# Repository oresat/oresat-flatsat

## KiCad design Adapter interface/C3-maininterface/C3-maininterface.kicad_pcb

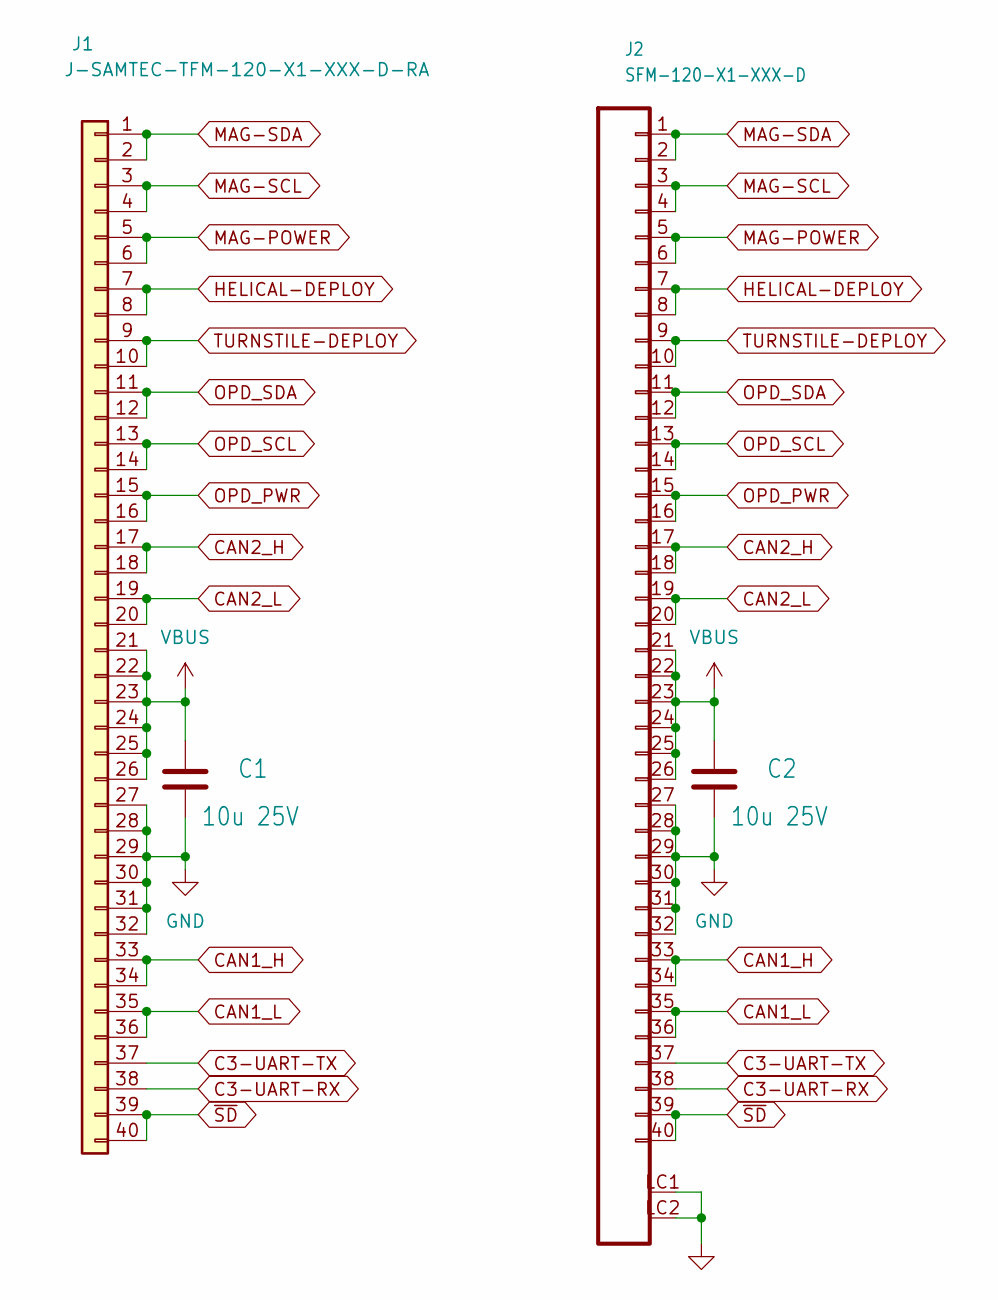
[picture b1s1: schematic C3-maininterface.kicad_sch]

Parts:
C1, C2: 10u 25V; C_1206_3216Metric
J1: J-SAMTEC-TFM-120-X1-XXX-D-RA; MPN TFM-120-01-L-D-RA
J2: SFM-120-X1-XXX-D; J-SAMTEC-SFM-120-X1-XXX-D

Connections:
C3-UART-RX: J1.38, J2.38
C3-UART-TX: J1.37, J2.37
CAN1_H: J1.33, J1.34, J2.33, J2.34
CAN1_L: J1.35, J1.36, J2.35, J2.36
CAN2_H: J1.17, J1.18, J2.17, J2.18
CAN2_L: J1.19, J1.20, J2.19, J2.20
GND: C1.2, C2.2, J1.27, J1.28, J1.29, J1.30, J1.31, J1.32, J2.27, J2.28, J2.29, J2.30, J2.31, J2.32, J2.LC1, J2.LC2
HELICAL-DEPLOY: J1.7, J1.8, J2.7, J2.8
MAG-POWER: J1.5, J1.6, J2.5, J2.6
MAG-SCL: J1.3, J1.4, J2.3, J2.4
MAG-SDA: J1.1, J1.2, J2.1, J2.2
OPD_PWR: J1.15, J1.16, J2.15, J2.16
OPD_SCL: J1.13, J1.14, J2.13, J2.14
OPD_SDA: J1.11, J1.12, J2.11, J2.12
TURNSTILE-DEPLOY: J1.9, J1.10, J2.9, J2.10
VBUS: C1.1, C2.1, J1.21, J1.22, J1.23, J1.24, J1.25, J1.26, J2.21, J2.22, J2.23, J2.24, J2.25, J2.26
~SD: J1.39, J1.40, J2.39, J2.40

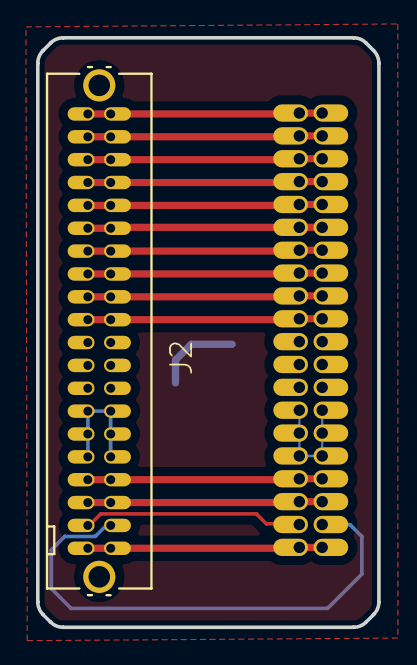
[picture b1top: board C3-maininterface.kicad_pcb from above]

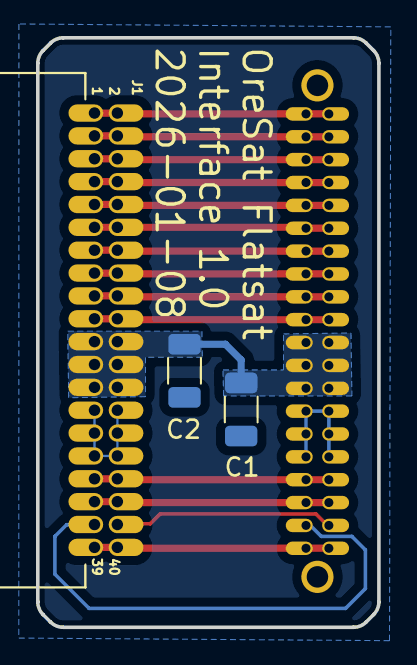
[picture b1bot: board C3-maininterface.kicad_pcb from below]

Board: 4 copper layers, 19.0 x 32.8 mm, 4 parts (3 on the bottom side), 17 nets.

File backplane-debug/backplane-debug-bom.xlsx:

OreSat Backplane Debug Connector Board v2.0
Qty | Parts | MFR | MPN | Description | DIST | DPN | DIST2 | DPN2 | DNS
1 | J1 | Harwin Inc. | M55-7101642R | CONN HEADER SMD R/A 16POS 1.27MM | Digi-Key | 952-3892-1-ND |  |  | DNS
1 | J2 | Amphenol ICC (FCI) | 86130161014345E1LF | QKE CONN SOCKET IDC 16 POS 2.54MM | Digi-Key | 609-86130161014345E1LF-ND

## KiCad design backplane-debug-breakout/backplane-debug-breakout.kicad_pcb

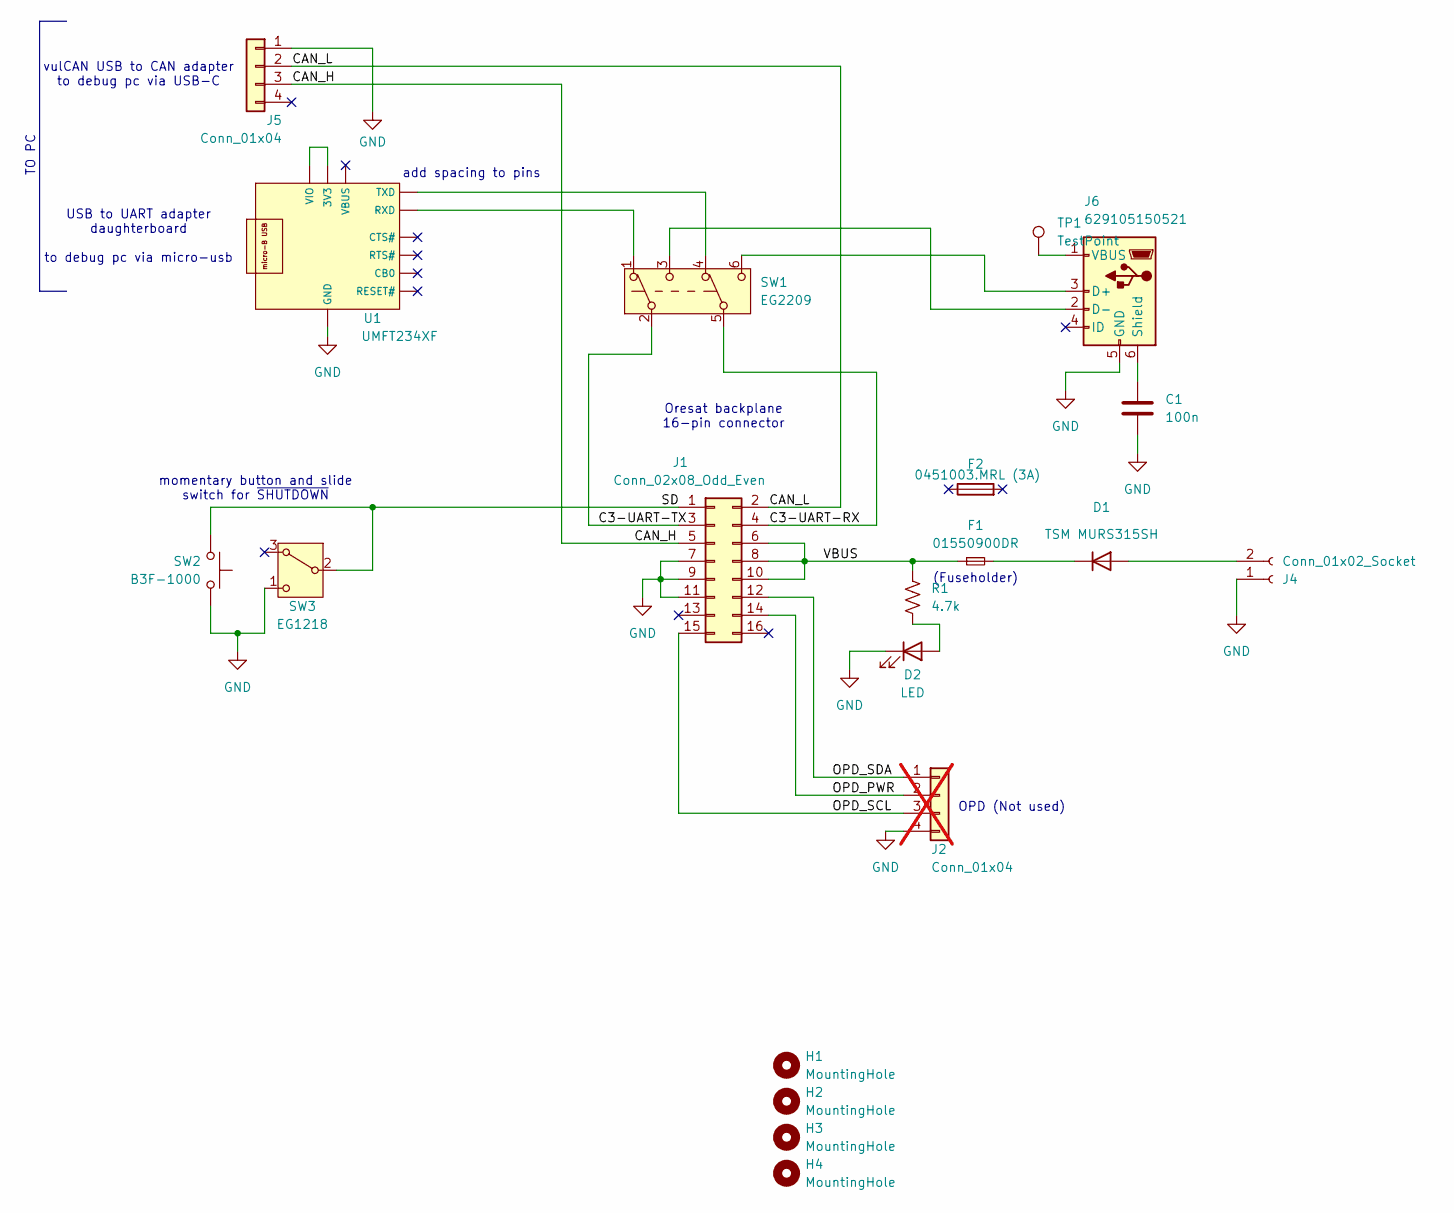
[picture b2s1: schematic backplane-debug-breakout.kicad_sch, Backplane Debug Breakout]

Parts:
C1: 100n; C_0603_1608Metric; MPN TMK107BJ104KAHT
D1: TSM MURS315SH; Diode TSM MURS315SH; MPN MUR315SH
D2: LED; LED_0603_1608Metric_Pad1.05x0.95mm_HandSolder; MPN 150060RS75000
F1: 01550900DR; Littelfuse 155900DR; MPN 01550900DR
F2: 0451003.MRL (3A); MPN 0451003.MRL
H1, H2, H3, H4: MountingHole; MountingHole_3mm_no_copper
J1: Conn_02x08_Odd_Even; IDC-Header_2x08_P2.54mm_Vertical; MPN 61201621621
J2: Conn_01x04; PinHeader_1x04_P2.54mm_Vertical; MPN 0757570441; not fitted
J4: Conn_01x02_Socket; PHOENIX_1995499; MPN 1995499
J5: Conn_01x04; PinHeader_1x04_P2.54mm_Vertical; MPN 0757570441
J6: 629105150521; USB_Micro-B_Wuerth_629105150521_CircularHoles; MPN 629105150521
R1: 4.7k; R_0603_1608Metric_Pad0.98x0.95mm_HandSolder; MPN RMCF0603FT4K70
SW1: EG2209; EG2209 DPDT; MPN EG2209
SW2: B3F-1000; SW_PUSH_6mm; MPN B3F-1000
SW3: EG1218; PinHeader_1x03_P2.54mm_Vertical; MPN EG1218
TP1: TestPoint; TestPoint-0.75mm-th
U1: UMFT234XF; MPN UMFT234XF

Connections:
/C3-UART-RX: J1.4, SW1.5 (B)
/C3-UART-TX: J1.3, SW1.2 (B)
/CAN_H: J1.5, J5.3
/CAN_L: J1.2, J5.2
/OPD_PWR: J1.14, J2.2
/OPD_SCL: J1.15, J2.3
/OPD_SDA: J1.12, J2.1
/SD: J1.1, SW2.2, SW3.2 (B)
/VBUS: F1.1, J1.6, J1.8, J1.10, R1.1
GND: C1.2, D2.1 (K), J1.7, J1.9, J1.11, J2.4, J4.1, J5.1, J6.5 (GND), SW2.1, SW3.1 (C), U1.P4 (GND)
unnamed: D1.2 (A), J4.2
unnamed: D1.1 (K), F1.2
unnamed: D2.2 (A), R1.2
unnamed: J6.3 (D+), SW1.6 (C)
unnamed: J6.2 (D-), SW1.3 (C)
unnamed: C1.1, J6.6 (Shield)
unnamed: J6.1 (VBUS), TP1.1
unnamed: U1.P2 (3V3), U1.P3 (VIO)
unnamed: SW1.1 (A), U1.P9 (RXD)
unnamed: SW1.4 (A), U1.P7 (TXD)

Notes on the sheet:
Oresat backplane 16-pin connector
vulCAN USB to CAN adapter to debug pc via USB-C
momentary button and slide switch for ~{SHUTDOWN}
TO PC
(Fuseholder)
USB to UART adapter daughterboard to debug pc via micro-usb
add spacing to pins
OPD (Not used)

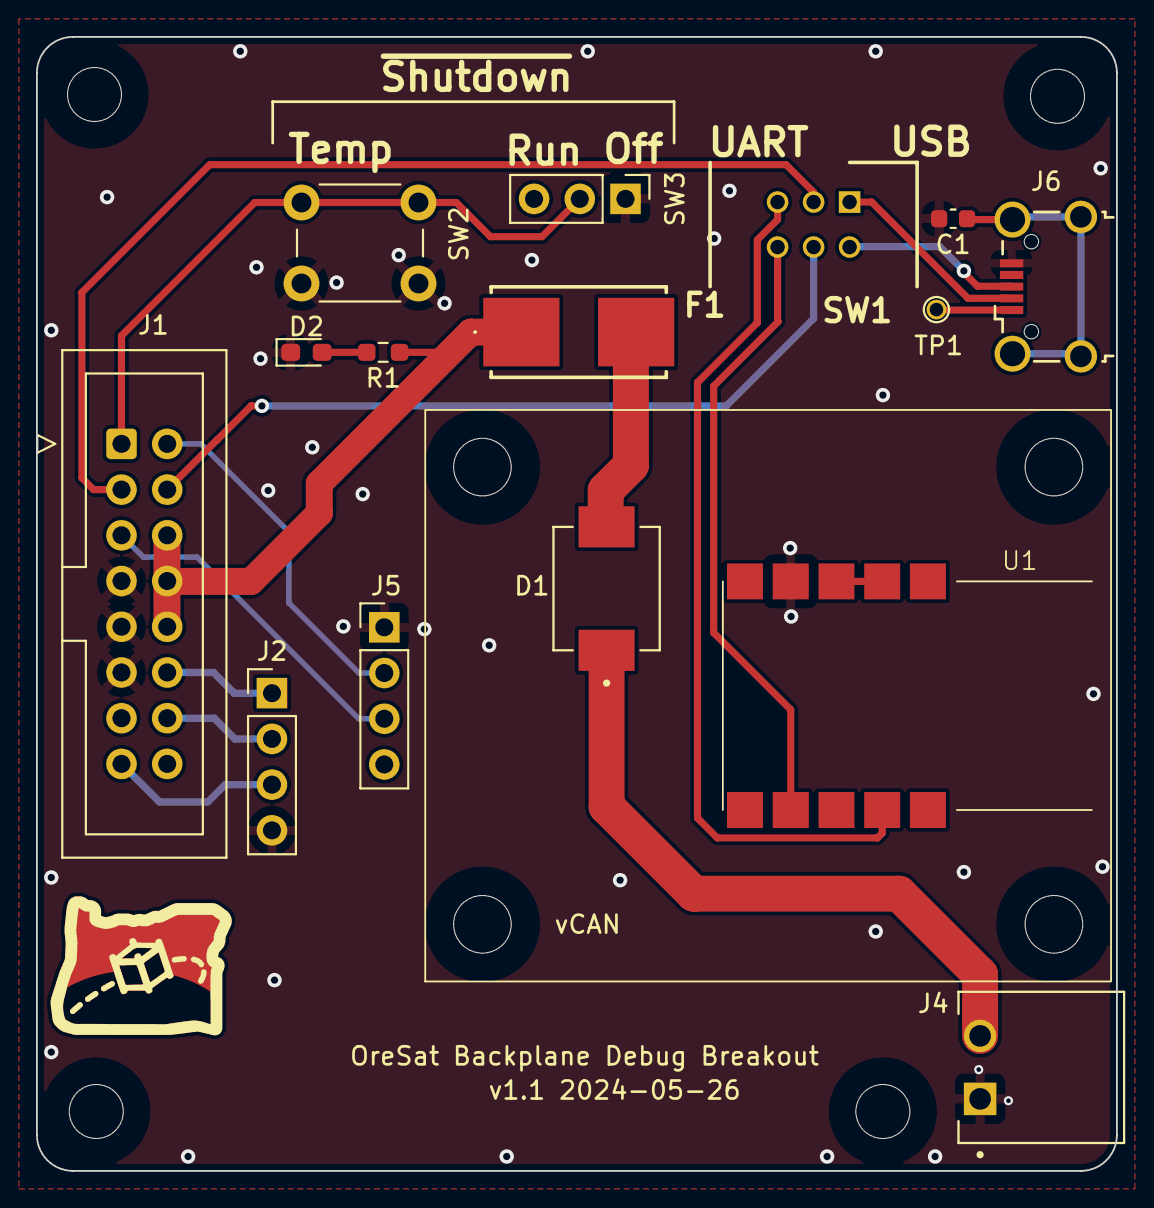
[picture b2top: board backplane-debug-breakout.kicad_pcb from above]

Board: 2 copper layers, 60.0 x 63.0 mm, 21 parts (0 on the bottom side), 20 nets.

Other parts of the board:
Logo: logo-small
vCAN: vulCAN

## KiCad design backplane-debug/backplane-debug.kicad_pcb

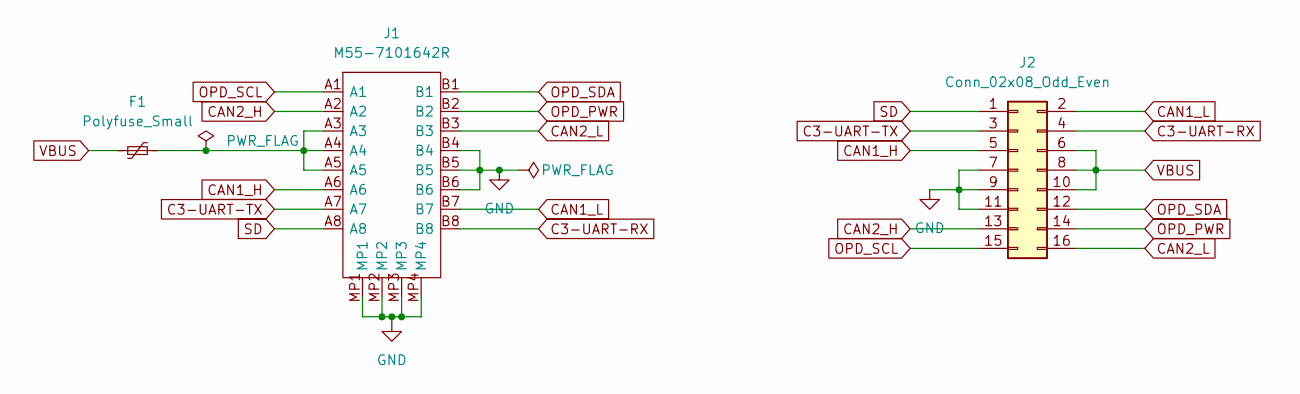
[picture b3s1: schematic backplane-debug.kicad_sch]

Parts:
F1: Polyfuse_Small; Fuse_1206_3216Metric
J1: M55-7101642R; M557101642R; Manufacturer_Part_Number M55-7101642R
J2: Conn_02x08_Odd_Even; IDC-Header_2x08_P2.54mm_Vertical

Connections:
C3-UART-RX: J1.B8, J2.4
C3-UART-TX: J1.A7, J2.3
CAN1_H: J1.A6, J2.5
CAN1_L: J1.B7, J2.2
CAN2_H: J1.A2, J2.13
CAN2_L: J1.B3, J2.16
GND: J1.B4, J1.B5, J1.B6, J1.MP1, J1.MP2, J1.MP3, J1.MP4, J2.7, J2.9, J2.11
unnamed: F1.2, J1.A3, J1.A4, J1.A5
OPD_PWR: J1.B2, J2.14
OPD_SCL: J1.A1, J2.15
OPD_SDA: J1.B1, J2.12
SD: J1.A8, J2.1
VBUS: F1.1, J2.6, J2.8, J2.10

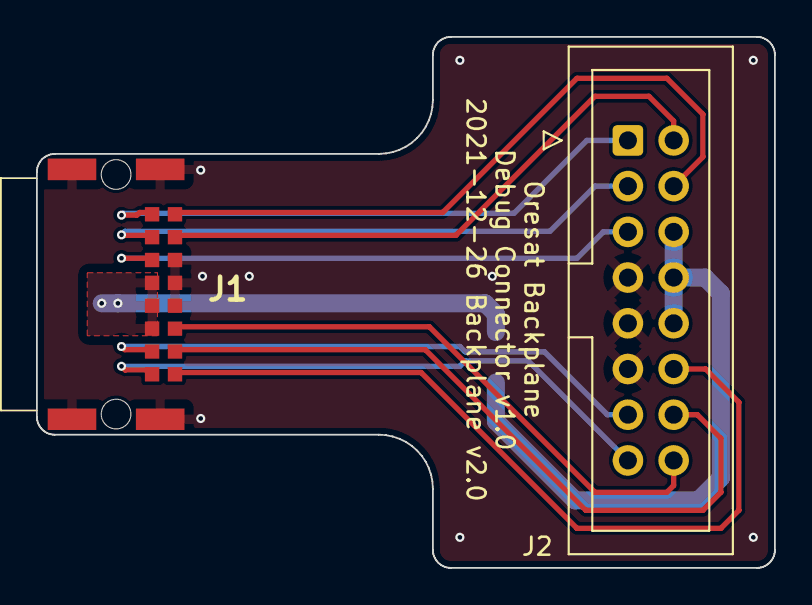
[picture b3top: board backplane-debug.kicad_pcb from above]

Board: 2 copper layers, 41.0 x 29.5 mm, 3 parts (1 on the bottom side), 13 nets.

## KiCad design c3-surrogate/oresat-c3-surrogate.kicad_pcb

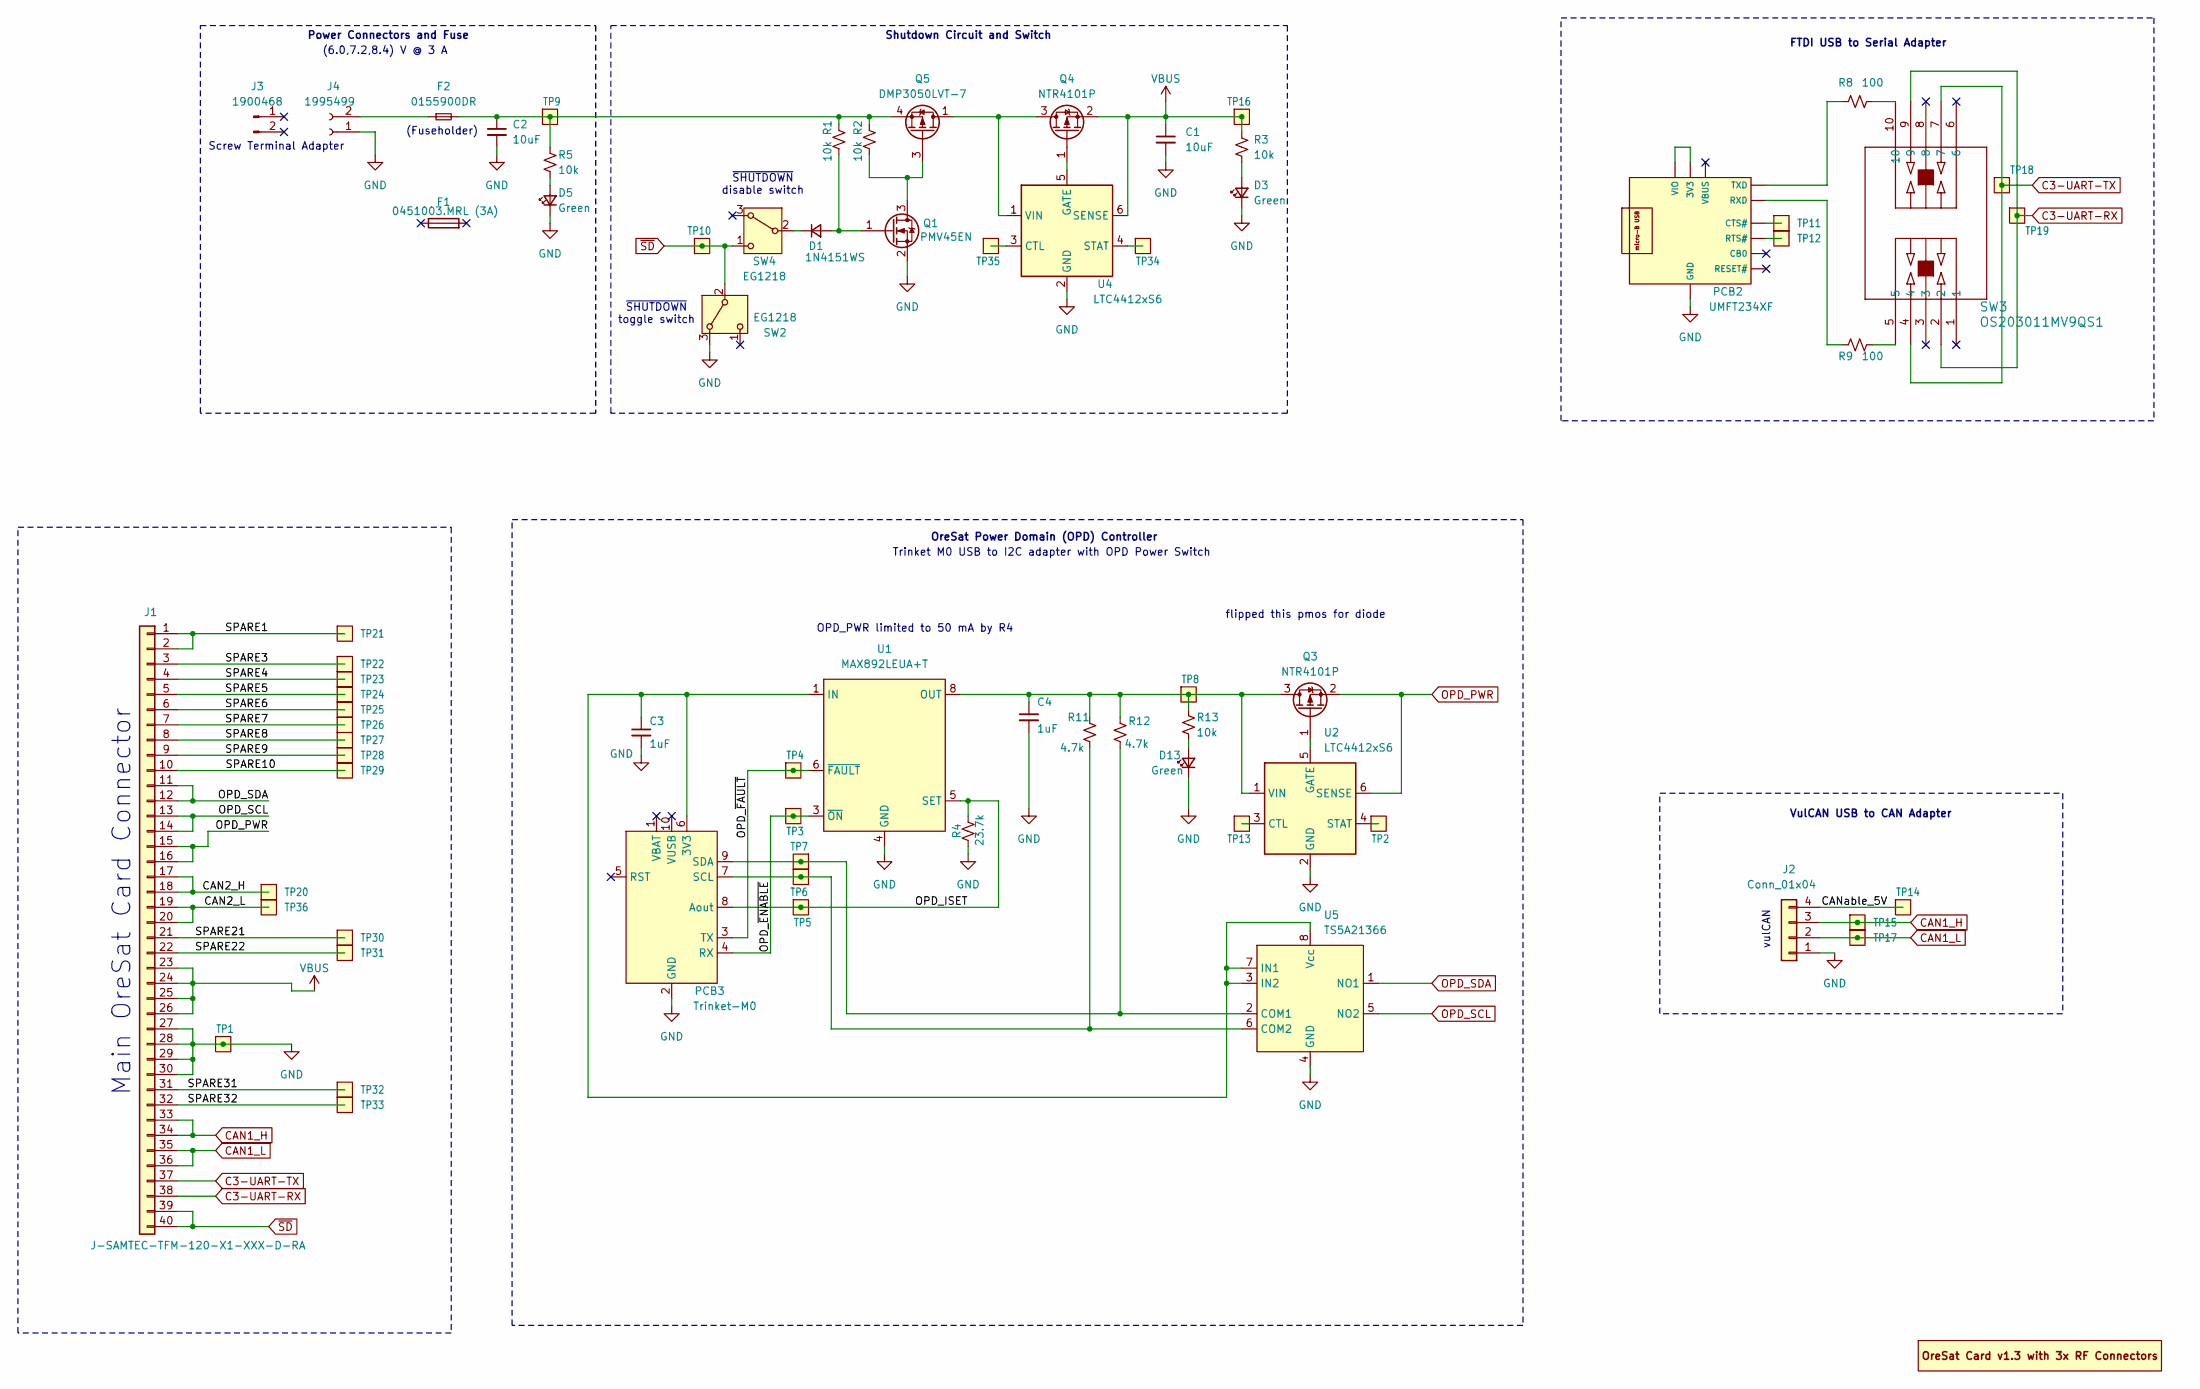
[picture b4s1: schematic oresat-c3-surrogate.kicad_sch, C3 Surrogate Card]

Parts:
C1, C2: 10uF; C_0603_1608Metric_Pad1.08x0.95mm_HandSolder; MPN GRT188R61C106KE13D
C3, C4: 1uF; C_0603_1608Metric_Pad1.08x0.95mm_HandSolder; MPN TMK107BJ105KAHT
D1: 1N4151WS; D_SOD-323F; MPN 1N4151WS-E3-08
D3, D5, D13: Green; LED_0603_1608Metric_Pad1.05x0.95mm_HandSolder; MPN IN-S63AT5G
F1: 0451003.MRL (3A); MPN 0451003.MRL
F2: 0155900DR; Littelfuse 155900DR; MPN 01550900DR
J1: J-SAMTEC-TFM-120-X1-XXX-D-RA; MPN TFM-120-01-L-D-RA
J2: Conn_01x04; PinHeader_1x04_P2.54mm_Vertical; MPN 0757570441
J3: 1900468; MPN 1900468
J4: 1995499; PHOENIX_1995499; MPN 1995499
PCB1: ORESAT-CARD-V1.3-GENERIC-3RF; ORESAT-CARD-V1.3-3RF; MPN N/A
PCB2: UMFT234XF; MPN UMFT234XF
PCB3: Trinket-M0; Adafruit-Trinket; MPN 3500
Q1: PMV45EN; SOT23; MPN PMV45EN2R
Q3, Q4: NTR4101P; SOT-23; MPN NTR4101PT1G
Q5: DMP3050LVT-7; SOT-23-6; MPN DMP3050LVT-7
R1, R2, R3, R5, R13: 10k; R_0603_1608Metric_Pad0.98x0.95mm_HandSolder; MPN RMCF0603FT10K0
R4: 23.7k; R_0603_1608Metric_Pad0.98x0.95mm_HandSolder; MPN RMCF0603FT23K7
R8, R9: 100; R_0603_1608Metric_Pad0.98x0.95mm_HandSolder; MPN RMCF0603FT100R
R11, R12: 4.7k; R_0603_1608Metric_Pad0.98x0.95mm_HandSolder; MPN RMCF0603FT4K70
SW2, SW4: EG1218; PinHeader_1x03_P2.54mm_Vertical; MPN EG1218
SW3: OS203011MV9QS1; DP3T_OS203011MV9QS1_CNK; MPN OS203011MV9QS1
TP1, TP2, TP3, TP4, TP5, TP6, TP7, TP8, TP9, TP10, TP11, TP12, TP13, TP14, TP15, TP16, TP17, TP18, TP19, TP20, TP21, TP22, TP23, TP24, TP25, TP26, TP27, TP28, TP29, TP30, TP31, TP32, TP33, TP34, TP35, TP36: Test-Point; TestPoint-0.75mm-th; MPN N/A
U1: MAX892LEUA+T; LINEAR-MSOP-8-AND-MAXIM-UMAX-8-21-0036; MPN MAX892LEUA+
U2, U4: LTC4412xS6; TSOT-23-6; MPN LTC4412ES6#TRPBF
U5: TS5A21366; VSSOP-8_2.3x2mm_P0.5mm; MPN TS5A21366DCUR

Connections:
/CAN2_H: J1.17, J1.18, TP20.1
/CAN2_L: J1.19, J1.20, TP36.1
/CANable_5V: J2.4, TP14.1
/OPD_ISET: PCB3.8 (Aout), R4.1, TP5.1, U1.5 (SET)
/OPD_~ENABLE: PCB3.4 (RX), TP3.1, U1.3 (~ON)
/OPD_~FAULT: PCB3.3 (TX), TP4.1, U1.6 (~FAULT)
/SPARE1: J1.1, J1.2, TP21.1
/SPARE3: J1.3, TP22.1
/SPARE4: J1.4, TP23.1
/SPARE5: J1.5, TP24.1
/SPARE6: J1.6, TP25.1
/SPARE7: J1.7, TP26.1
/SPARE8: J1.8, TP27.1
/SPARE9: J1.9, TP28.1
/SPARE10: J1.10, TP29.1
/SPARE21: J1.21, TP30.1
/SPARE22: J1.22, TP31.1
/SPARE31: J1.31, TP32.1
/SPARE32: J1.32, TP33.1
C3-UART-RX: J1.38, SW3.2, SW3.9, TP19.1
C3-UART-TX: J1.37, SW3.4, SW3.7, TP18.1
CAN1_H: J1.33, J1.34, J2.3, TP15.1
CAN1_L: J1.35, J1.36, J2.2, TP17.1
GND: C1.2, C2.2, C3.2, C4.2, D3.1 (K), D5.1 (K), D13.1 (K), J1.27, J1.28, J1.29, J1.30, J2.1, J4.1, PCB2.P4 (GND), PCB3.2 (GND), Q1.2 (S), R4.2, SW2.3 (A), TP1.1, U1.4 (GND), U2.2 (GND), U4.2 (GND), U5.4 (GND)
unnamed: D1.2 (A), Q1.1 (G), R1.2
unnamed: D1.1 (K), SW4.2 (B)
unnamed: D3.2 (A), R3.2
unnamed: D5.2 (A), R5.2
unnamed: D13.2 (A), R13.2
unnamed: F2.1, J4.2
unnamed: PCB2.P2 (3V3), PCB2.P3 (VIO)
unnamed: PCB2.P10 (CTS#), TP11.1
unnamed: PCB2.P8 (RTS#), TP12.1
unnamed: PCB2.P9 (RXD), R9.1
unnamed: PCB2.P7 (TXD), R8.1
unnamed: C3.1, PCB3.6 (3V3), U1.1 (IN), U1.2 (IN_2), U5.3 (IN2), U5.7 (IN1), U5.8 (Vcc)
unnamed: PCB3.7 (SCL), R11.2, TP6.1, U5.6 (COM2)
unnamed: PCB3.9 (SDA), R12.2, TP7.1, U5.2 (COM1)
unnamed: Q1.3 (D), Q5.3 (G), R2.2
unnamed: C4.1, Q3.3 (D), R11.1, R12.1, R13.1, TP8.1, U1.7 (OUT_2), U1.8 (OUT), U2.1 (VIN)
unnamed: Q3.1 (G), U2.5 (GATE)
unnamed: Q4.3 (D), Q5.1 (D), Q5.2 (D), Q5.5 (D), Q5.6 (D), U4.1 (VIN)
unnamed: Q4.1 (G), U4.5 (GATE)
unnamed: C2.1, F2.2, Q5.4 (S), R1.1, R2.1, R5.1, TP9.1
unnamed: R8.2, SW3.10
unnamed: R9.2, SW3.5
unnamed: TP13.1, U2.3 (CTL)
unnamed: TP2.1, U2.4 (STAT)
unnamed: TP35.1, U4.3 (CTL)
unnamed: TP34.1, U4.4 (STAT)
OPD_PWR: J1.15, J1.16, Q3.2 (S), U2.6 (SENSE)
OPD_SCL: J1.13, J1.14, U5.5 (NO2)
OPD_SDA: J1.11, J1.12, U5.1 (NO1)
VBUS: C1.1, J1.23, J1.24, J1.25, J1.26, Q4.2 (S), R3.1, TP16.1, U4.6 (SENSE)
~SD: J1.39, J1.40, SW2.2 (B), SW4.1 (C), TP10.1

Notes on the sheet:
Main OreSat Card Connector
(6.0,7.2,8.4) V @ 3 A
OreSat Power Domain (OPD) Controller
Screw Terminal Adapter
flipped this pmos for diode
(Fuseholder)
VulCAN USB to CAN Adapter
~{SHUTDOWN} toggle switch
Power Connectors and Fuse
Trinket M0 USB to I2C adapter with OPD Power Switch
FTDI USB to Serial Adapter
OPD_PWR limited to 50 mA by R4
~{SHUTDOWN} disable switch
Shutdown Circuit and Switch
vulCAN

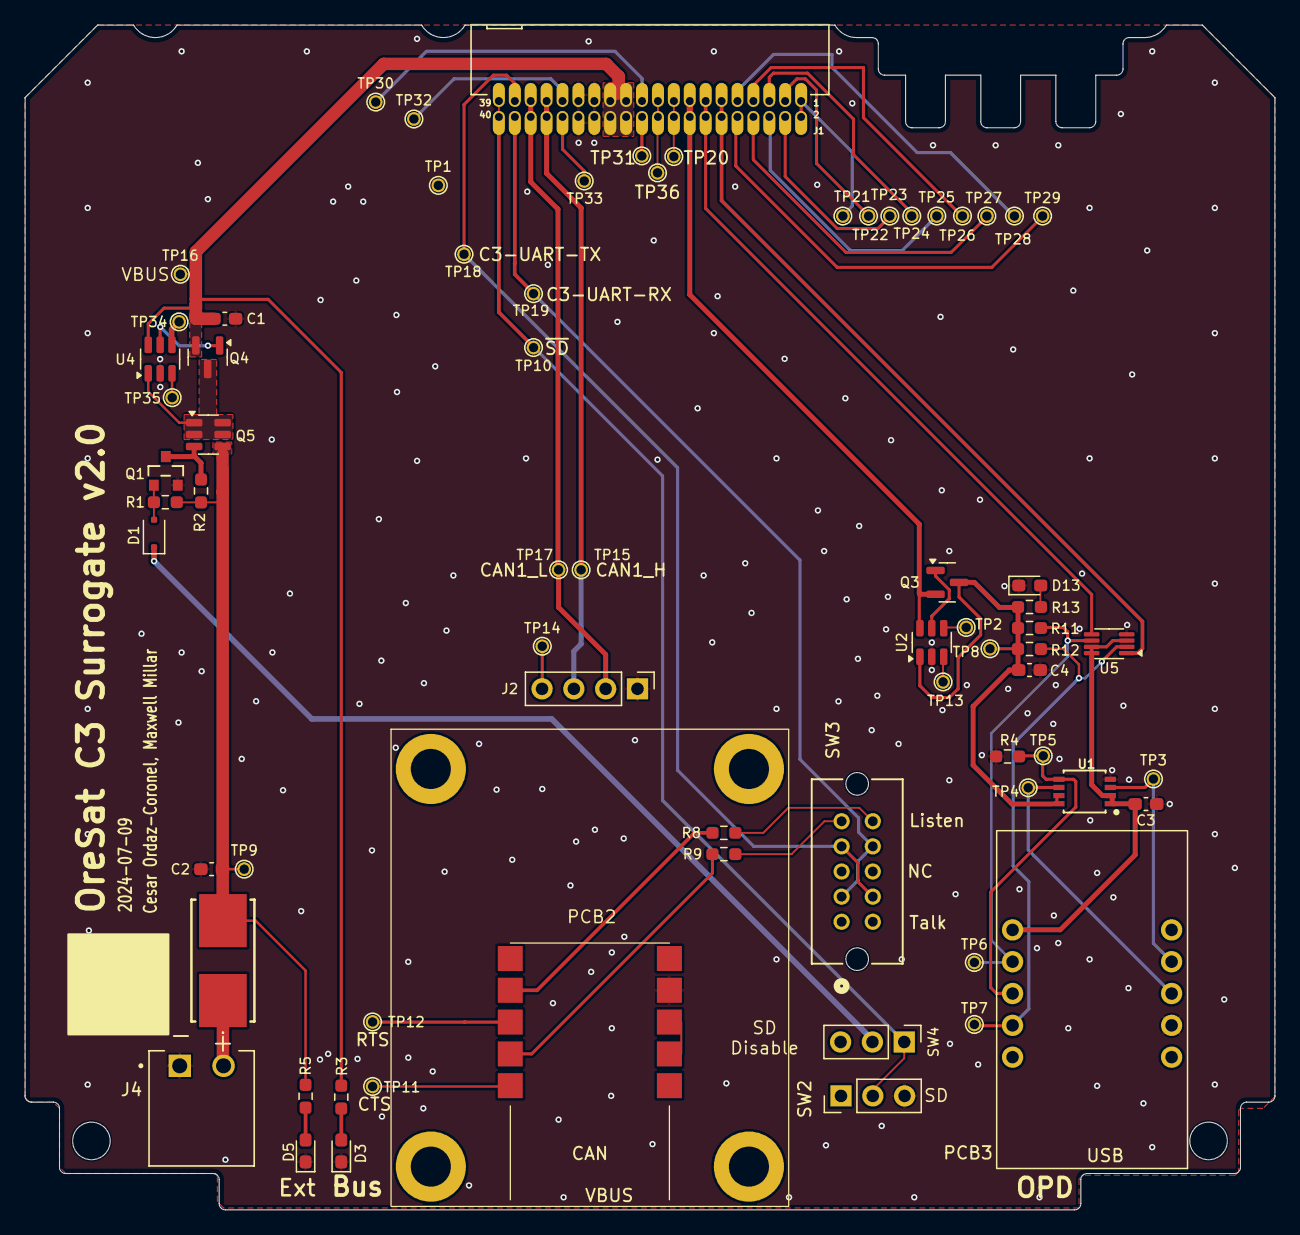
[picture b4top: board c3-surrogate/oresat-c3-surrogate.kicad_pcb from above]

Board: 2 copper layers, 99.8 x 94.6 mm, 73 parts (0 on the bottom side), 55 nets.

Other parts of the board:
vCAN: vulCAN

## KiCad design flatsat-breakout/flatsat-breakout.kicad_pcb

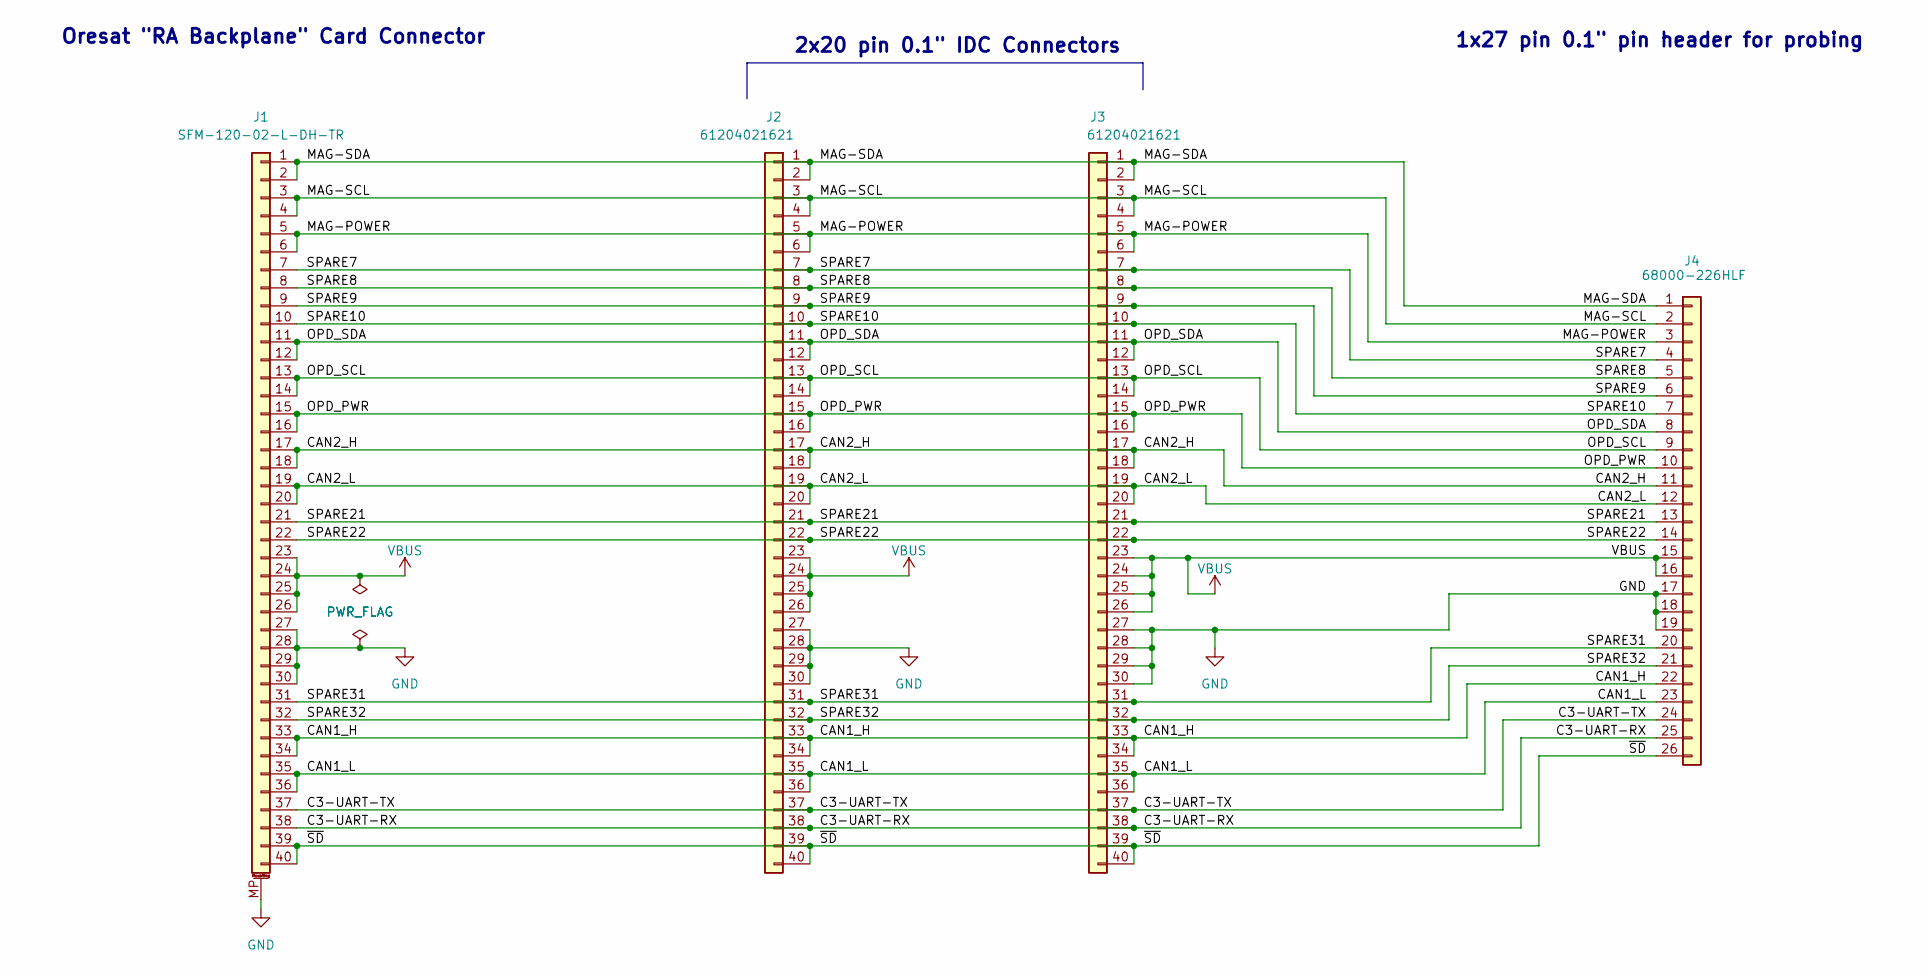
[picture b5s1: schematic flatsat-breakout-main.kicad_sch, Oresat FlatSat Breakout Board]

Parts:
J1: SFM-120-02-L-DH-TR; SFM-120-02-X-DH; MPN SFM-120-02-L-DH-TR
J2, J3: 61204021621; IDC-Header_2x20_P2.54mm_Vertical; MPN 61204021621
J4: 68000-226HLF; PinHeader_1x26_P2.54mm_Vertical; MPN 68000-226HLF

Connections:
/C3-UART-RX: J1.38, J2.38, J3.38, J4.25
/C3-UART-TX: J1.37, J2.37, J3.37, J4.24
/CAN1_H: J1.33, J1.34, J2.33, J2.34, J3.33, J3.34, J4.22
/CAN1_L: J1.35, J1.36, J2.35, J2.36, J3.35, J3.36, J4.23
/CAN2_H: J1.17, J1.18, J2.17, J2.18, J3.17, J3.18, J4.11
/CAN2_L: J1.19, J1.20, J2.19, J2.20, J3.19, J3.20, J4.12
/MAG-POWER: J1.5, J1.6, J2.5, J2.6, J3.5, J3.6, J4.3
/MAG-SCL: J1.3, J1.4, J2.3, J2.4, J3.3, J3.4, J4.2
/MAG-SDA: J1.1, J1.2, J2.1, J2.2, J3.1, J3.2, J4.1
/OPD_PWR: J1.15, J1.16, J2.15, J2.16, J3.15, J3.16, J4.10
/OPD_SCL: J1.13, J1.14, J2.13, J2.14, J3.13, J3.14, J4.9
/OPD_SDA: J1.11, J1.12, J2.11, J2.12, J3.11, J3.12, J4.8
/SPARE7: J1.7, J2.7, J3.7, J4.4
/SPARE8: J1.8, J2.8, J3.8, J4.5
/SPARE9: J1.9, J2.9, J3.9, J4.6
/SPARE10: J1.10, J2.10, J3.10, J4.7
/SPARE21: J1.21, J2.21, J3.21, J4.13
/SPARE22: J1.22, J2.22, J3.22, J4.14
/SPARE31: J1.31, J2.31, J3.31, J4.20
/SPARE32: J1.32, J2.32, J3.32, J4.21
/~SD: J1.39, J1.40, J2.39, J2.40, J3.39, J3.40, J4.26
GND: J1.27, J1.28, J1.29, J1.30, J1.MP (MountPin), J2.27, J2.28, J2.29, J2.30, J3.27, J3.28, J3.29, J3.30, J4.17, J4.18, J4.19
VBUS: J1.23, J1.24, J1.25, J1.26, J2.23, J2.24, J2.25, J2.26, J3.23, J3.24, J3.25, J3.26, J4.15, J4.16

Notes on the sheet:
1x27 pin 0.1" pin header for probing
Oresat "RA Backplane" Card Connector
2x20 pin 0.1" IDC Connectors

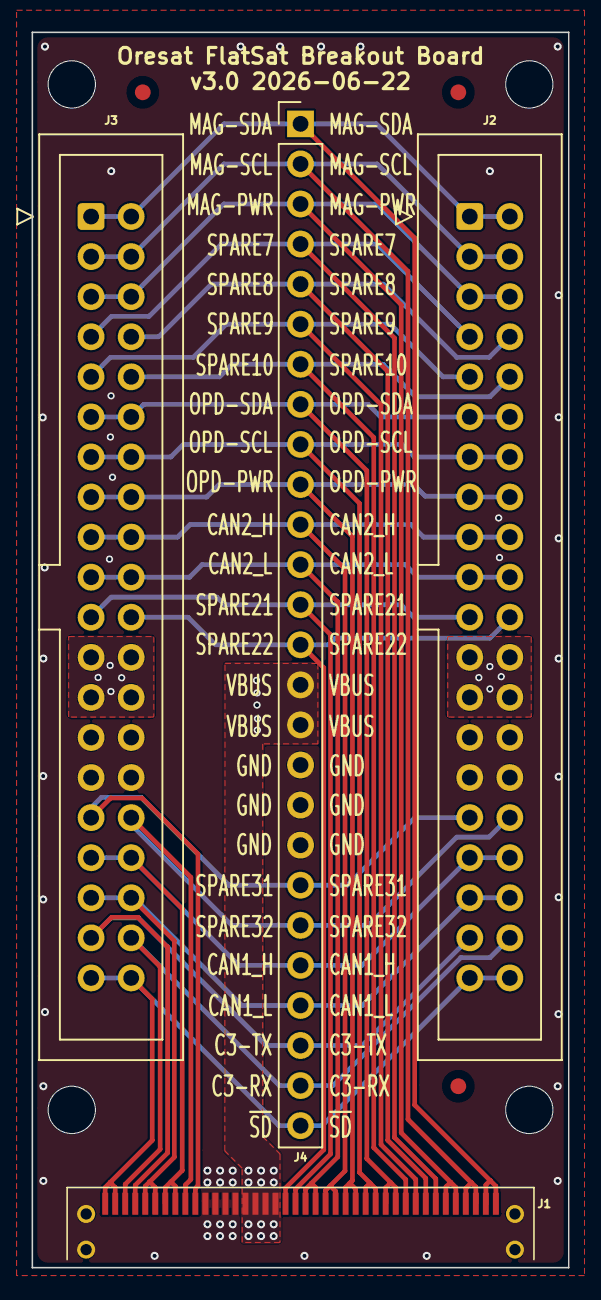
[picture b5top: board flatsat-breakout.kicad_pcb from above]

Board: 4 copper layers, 34.0 x 78.3 mm, 4 parts (0 on the bottom side), 23 nets.

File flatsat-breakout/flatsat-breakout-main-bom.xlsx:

OreSat FlatSat Card Breakout Board v2.0
Qty | Parts | MFR | MPN | Description | DIST | DPN | DIST2 | DPN2 | DNS
1 | J1 | Samtec Inc. | SFM-120-02-L-DH-TR | CONN RCPT 40P 0.05 GOLD SMD R/A | Digi-Key | SAM14509CT-ND |  |  | DNS
2 | J2, J3 | Würth Elektronik | 61204021621 | CONN HEADER VERT 40POS 2.54MM | Digi-Key | 732-5401-ND
1 | J4 | Amphenol ICC (FCI) | 68000-227HLF | CONN HEADER VERT 27POS 2.54MM | Digi-Key | 68000-227HLF-ND
1 | J5 | Würth Elektronik | 61201621621 | CONN HEADER VERT 16POS 2.54MM | Digi-Key | 732-2095-ND

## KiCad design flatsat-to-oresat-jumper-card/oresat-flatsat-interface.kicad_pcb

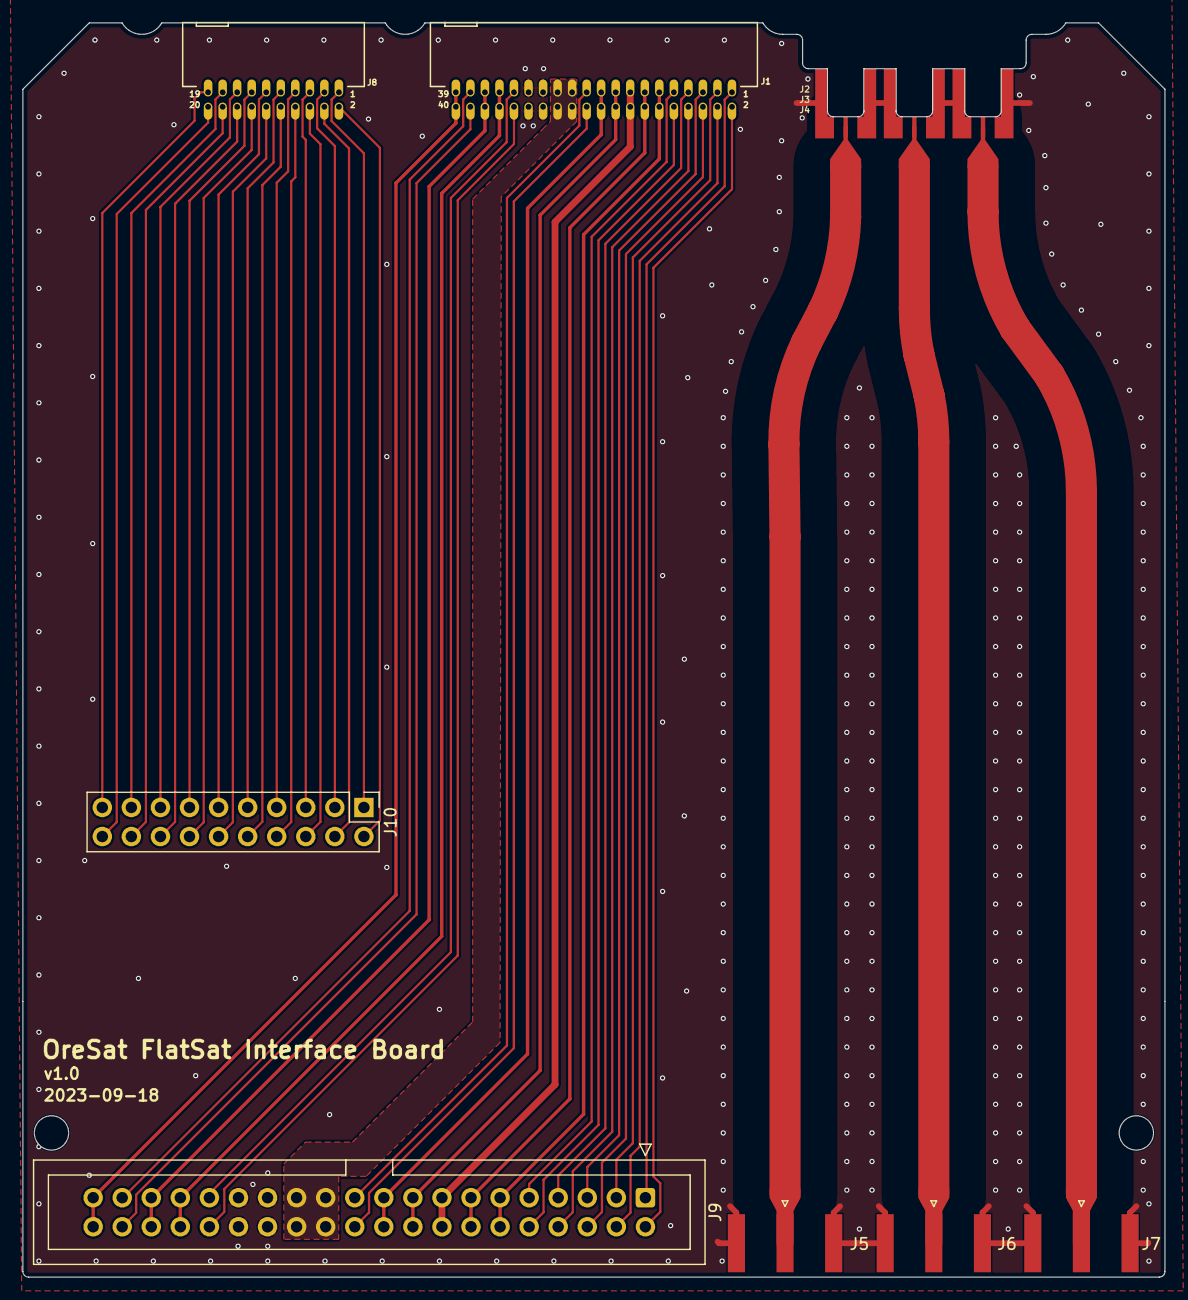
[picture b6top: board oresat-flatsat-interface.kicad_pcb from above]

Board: 2 copper layers, 99.8 x 109.6 mm, 11 parts (0 on the bottom side), 49 nets.

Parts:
J1: J-SAMTEC-TFM-120-01-L-D-RA; J-SAMTEC-TFM-120-X1-XXX-D-RA-small-pads
J2, J3, J4: 733000020; J-MOLEX-SMPM-073300-002X
J5, J6, J7: Conn_Coaxial; SMA_Amphenol_132289_EdgeMount
J8: J-SAMTEC-TFM-110-01-L-D-RA; J-SAMTEC-TFM-110-X1-XXX-D-RA-small-pads
J9: Conn_01x40; IDC-Header_2x20_P2.54mm_Vertical
J10: Conn_01x20; PinHeader_2x10_P2.54mm_Vertical
PCB1: ORESAT-CARD-V1.3-FLATSAT

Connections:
/C3-UART-RX: J1.38, J9.38
/C3-UART-TX: J1.37, J9.37
/CAN1_H: J1.33, J1.34, J9.33, J9.34
/CAN1_L: J1.35, J1.36, J9.35, J9.36
/CAN2_H: J1.17, J1.18, J9.17, J9.18
/CAN2_L: J1.19, J1.20, J9.19, J9.20
/OPD_PWR: J1.15, J1.16, J9.15, J9.16
/OPD_SCL: J1.13, J1.14, J9.13, J9.14
/OPD_SDA: J1.11, J1.12, J9.11, J9.12
/ORESAT_~SD: J1.39, J1.40, J9.39, J9.40
/SPARE1: J1.1, J9.1
/SPARE2: J1.2, J9.2
/SPARE3: J1.3, J9.3
/SPARE4: J1.4, J9.4
/SPARE5: J1.5, J9.5
/SPARE6: J1.6, J9.6
/SPARE7: J1.7, J9.7
/SPARE8: J1.8, J9.8
/SPARE9: J1.9, J9.9
/SPARE10: J1.10, J9.10
/SPARE21: J1.21, J9.21
/SPARE22: J1.22, J9.22
/SPARE31: J1.31, J9.31
/SPARE32: J1.32, J9.32
GND: J1.27, J1.28, J1.29, J1.30, J2.SHLD, J3.SHLD, J4.SHLD, J5.2 (Ext), J6.2 (Ext), J7.2 (Ext), J9.27, J9.28, J9.29, J9.30
unnamed: J2.SIG, J5.1 (In)
unnamed: J3.SIG, J6.1 (In)
unnamed: J4.SIG, J7.1 (In)
unnamed: J8.1, J10.1
unnamed: J8.2, J10.2
unnamed: J8.3, J10.3
unnamed: J8.4, J10.4
unnamed: J8.5, J10.5
unnamed: J8.6, J10.6
unnamed: J8.7, J10.7
unnamed: J8.8, J10.8
unnamed: J8.9, J10.9
unnamed: J8.10, J10.10
unnamed: J8.11, J10.11
unnamed: J8.12, J10.12
unnamed: J8.13, J10.13
unnamed: J8.14, J10.14
unnamed: J8.15, J10.15
unnamed: J8.16, J10.16
unnamed: J8.17, J10.17
unnamed: J8.18, J10.18
unnamed: J8.19, J10.19
unnamed: J8.20, J10.20
VBUS: J1.23, J1.24, J1.25, J1.26, J9.23, J9.24, J9.25, J9.26
